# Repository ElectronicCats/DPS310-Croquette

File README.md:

# ElectronicCats DPS310XT

## Summary

The [DPS310](https://www.infineon.com/dgdl/Infineon-DPS310-DS-v01_00-EN.pdf?fileId=5546d462576f34750157750826c42242) is a miniaturized digital barometric air pressure sensor with a high accuracy and a low current consumption, capable of measuring both pressure and temperature. The internal signal processor converts the output from the pressure and temperature sensor elements to 24 bit results. Each unit is individually calibrated, the calibration coefficients calculated during this process are stored in the calibration registers. The available raw data of the sensor can be calibrated by using the pre-calibrated coefficients as they are used in the application to convert the measurement results to high accuracy pressure and temperature values.

Sensor measurements and calibration coefficients are available through the serial I2C or SPI interface.

## Key Features and Applications
* Supply voltage range 1.7V to 3.6V
* Operation range 300hPa – 1200hPa
* Sensor’s precision 0.005hPa
* Relative accuracy ±0.06hPa
* Pressure temperature sensitivity of 0.5Pa/K
* Temperature accuracy  ±0.5C°
* Applications
  * Wearable applications, sport and fitness activities tracking
  * Drones automatic pilot, fix point flying
  * Indoor navigation, altitude metering

## Known Issues

### Temperature Measurement Issue
There could be a problem with temperature measurement of the DPS310. If your DPS310 indicates a temperature around 60 °C although you expect around room temperature, e.g. 20 °C, please call the function correctTemp() as included in the library to fix this issue.

In case you need additional help, please do not hesitate to open an issue in this repository.

### Interrupt mode
Interrupt mode not working reliably on XMC2Go for DPS310 right now.

### Additional Information
Please find the datasheet of the DPS310 [here](https://www.infineon.com/dgdl/Infineon-DPS310-DS-v01_00-EN.pdf?fileId=5546d462576f34750157750826c42242). It depends on the evaluation board which you are using or the respective configuration of the sensor on your PCB which communication protocol as well as addresses you need to use for communicating with the sensor.

## License
Electronic Cats invests time and resources providing this open source design, please support Electronic Cats and open-source hardware by purchasing products from Electronic Cats!

Designed by Electronic Cats.

Hardware released under an CERN Open Hardware Licence v1.2. See the LICENSE_HARDWARE file for more information.

Electronic Cats is a registered trademark, please do not use if you sell these PCBs.

10 Junuary 2020

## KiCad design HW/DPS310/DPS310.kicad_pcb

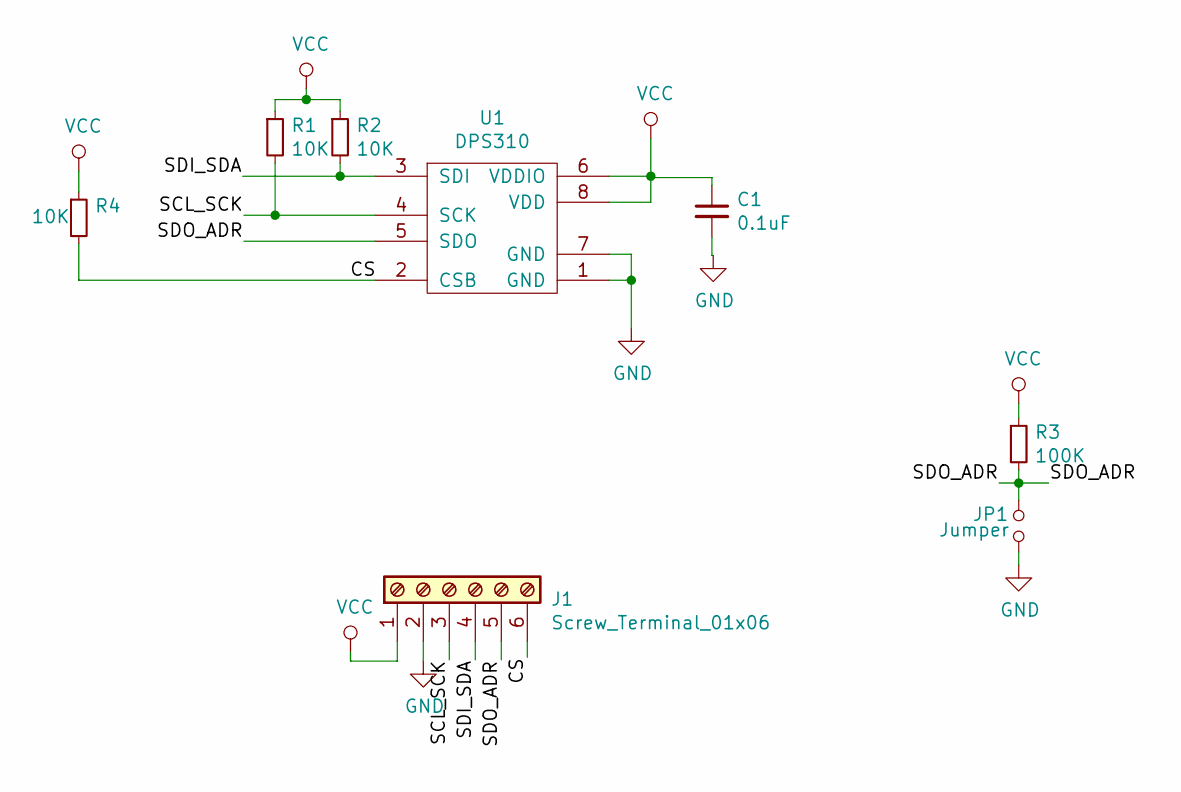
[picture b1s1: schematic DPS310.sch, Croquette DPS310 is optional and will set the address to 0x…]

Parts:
C1: 0.1uF; C_0805_2012Metric_Pad1.15x1.40mm_HandSolder
J1: Screw_Terminal_01x06; PinHeader_1x06_P2.54mm_Vertical
JP1: Jumper; SolderJumper-2_P1.3mm_Open_TrianglePad1.0x1.5mm
R1, R2: 10K; R_0805_2012Metric_Pad1.15x1.40mm_HandSolder
R3: 100K; R_0805_2012Metric_Pad1.15x1.40mm_HandSolder
R4: 10K; C_0805_2012Metric_Pad1.15x1.40mm_HandSolder
U1: DPS310; Bosch_LGA-8_2x2.5mm_P0.65mm_ClockwisePinNumbering

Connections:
/CS: J1.6, R4.2, U1.2 (CSB)
/SCL_SCK: J1.3, R1.2, U1.4 (SCK)
/SDI_SDA: J1.4, R2.2, U1.3 (SDI)
/SDO_ADR: J1.5, JP1.1, R3.2, U1.5 (SDO)
GND: C1.2, J1.2, JP1.2, U1.1 (GND), U1.7 (GND)
VCC: C1.1, J1.1, R1.1, R2.1, R3.1, R4.1, U1.6 (VDDIO), U1.8 (VDD)

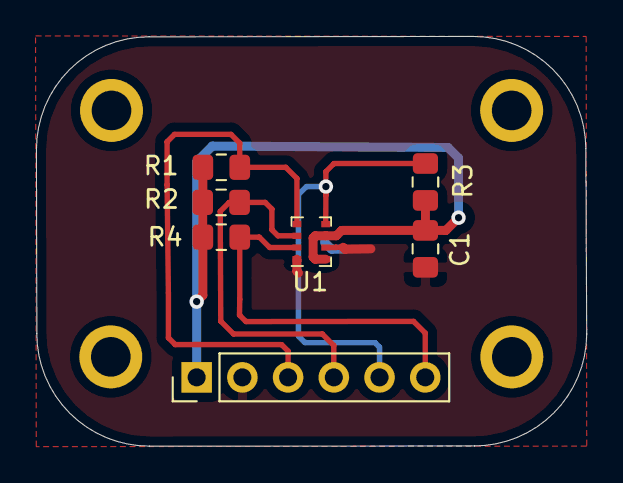
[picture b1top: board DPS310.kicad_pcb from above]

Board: 2 copper layers, 30.6 x 22.8 mm, 8 parts (1 on the bottom side), 6 nets.

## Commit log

2020-01-10 add schematic
2020-01-10 add gitignore
2020-01-18 fix name
2020-02-07 PCB view
2020-02-08 Last Revision
2020-02-09 update for SPI and I2C support
2020-02-11 Last revision of PCB
2020-02-11 New Last Revision
2020-02-24 fix cap and traces
